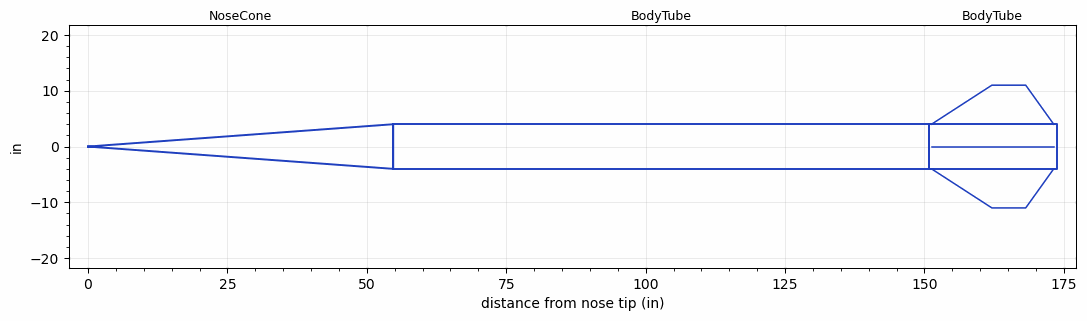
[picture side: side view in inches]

<RASAeroDocument>
 <FileVersion>2</FileVersion>
 <RocketDesign>
  <NoseCone>
   <Length>54.7243</Length>
   <Diameter>8</Diameter>
   <Shape>Conical</Shape>
   <Location>0</Location>
  </NoseCone>
  <BodyTube>
   <Length>95.9998</Length>
   <Diameter>8</Diameter>
   <Location>54.7243</Location>
  </BodyTube>
  <BodyTube>
   <Length>23</Length>
   <Diameter>8</Diameter>
   <Location>150.7241</Location>
   <Fin>
    <Count>4</Count>
    <Chord>21.9104</Chord>
    <Span>7.0079</Span>
    <SweepDistance>10.8268</SweepDistance>
    <TipChord>6.063</TipChord>
    <Thickness>0.25</Thickness>
    <Location>22.4616</Location>
    <AirfoilSection>Square</AirfoilSection>
   </Fin>
  </BodyTube>
  <Surface>Rough Camouflage Paint</Surface>
  <CD>0</CD>
  <ModifiedBarrowman>False</ModifiedBarrowman>
  <Turbulence>False</Turbulence>
  <UseBooster1>False</UseBooster1>
  <UseBooster2>False</UseBooster2>
  <Comments>Testing for stability --&gt; upthrust sim</Comments>
 </RocketDesign>
 <LaunchSite>
  <Altitude>0</Altitude>
  <Pressure>29.9214</Pressure>
  <RodAngle>0</RodAngle>
  <RodLength>3.2808</RodLength>
  <Temperature>59</Temperature>
  <WindSpeed>4.4739</WindSpeed>
 </LaunchSite>
 <Recovery>
  <Altitude1>0</Altitude1>
  <Altitude2>0</Altitude2>
  <DeviceType1>None</DeviceType1>
  <DeviceType2>None</DeviceType2>
  <Event1>False</Event1>
  <Event2>False</Event2>
  <Size1>0</Size1>
  <Size2>0</Size2>
  <EventType1>None</EventType1>
  <EventType2>None</EventType2>
  <CD1>0</CD1>
  <CD2>0</CD2>
 </Recovery>
 <SimulationList>
  <Simulation>
   <SustainerLaunchWt>103.4335</SustainerLaunchWt>
   <SustainerCG>113.7279</SustainerCG>
   <SustainerIgnitionDelay>0</SustainerIgnitionDelay>
   <Booster1SeparationDelay>0</Booster1SeparationDelay>
   <Booster1IgnitionDelay>0</Booster1IgnitionDelay>
   <IncludeBooster1>False</IncludeBooster1>
   <Booster2Delay>0</Booster2Delay>
   <IncludeBooster2>False</IncludeBooster2>
  </Simulation>
 </SimulationList>
</RASAeroDocument>
